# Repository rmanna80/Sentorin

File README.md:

# Sentorin

One platform for NFC/Bluetooth devices:

- **Pen** — tap to open the owner's business card; Bluetooth finding (BC832 / nRF52832).
- **Emergency bracelet** — tap opens an emergency page; full details only for verified responders, every view logged.

| Folder | Contents | Status |
|---|---|---|
| `hardware/pen-pcb` | KiCad project, revision 0.3 candidate | Not released for fabrication (see its README) |
| `backend/supabase` | Database schema, access rules, tests | Deployed to Supabase project `smartpen`; access tests pass there |
| `web/` | Tap pages (business card, emergency sign-in) | Written; not yet opened in a browser or hosted |
| `app/` | Owner app, iPhone + Android (Expo) | Typechecks and bundles; not yet run on a phone |
| `firmware/` | Pen firmware v1 beacon (nRF Connect SDK) | Written; not compiled or run on hardware |

## Backend tests

`backend/supabase/tests/local_auth_stub.sql` stands in for Supabase's auth schema on a plain Postgres.
Load the stub, then the migration, then run `access_rules_test.sql`.

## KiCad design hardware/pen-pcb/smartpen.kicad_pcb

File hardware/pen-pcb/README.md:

# Smart pen BLE tag — KiCad project, revision 0.3 candidate (NOT released for fabrication)

Open `smartpen.kicad_pro` in KiCad 7 or newer. No Gerbers, drill, CPL or STEP files are included:
ERC has not been run and the items under "Release blockers" are open.

## Changes in the 0.3 candidate (owner's measurement of Fanstel's EV-BC832 V2 Gerbers)

| Item | Fanstel EV board (owner-measured) | 0.2.1 | 0.3 candidate |
|---|---|---|---|
| Edge land, along the row | ~0.70 mm | 0.67 | **0.70** |
| Edge land, inner end (heel) from module centre | ~3.25 mm | 3.30 | **3.25** (matches) |
| Edge land, outer end (toe) from module centre | ~4.55 mm | 4.05 | **4.20** |
| Toe beyond the 7.8 mm module body | 0.65 mm | 0.15 | **0.30** |
| LGA land diameter | ~0.60 mm | 0.50 | **0.60** |
| Pitches (1.10 / 1.20 mm), pad counts | — | match | match |

- Fanstel's full land (toe at 4.55 mm) needs copper out to 9.1 mm plus edge clearance, i.e. a board about 9.6 mm wide, which does not fit even the 9.5 mm bore. The toe is therefore the one remaining deviation: 0.30 mm instead of 0.65 mm. Heel and width now follow Fanstel.
- **Board is now 8.9 mm wide and requires the 9.5 mm bore** (0.28 mm at the PCB corner; only 0.10 mm in a 9.14 mm bore).
- Strict antenna keep-out ends at x = 3.1 mm because Fanstel's first row of 0.6 mm LGA lands reaches x = 3.18 mm.
- DC/DC order confirmed by the owner from the EV-BC832 V2 schematic (DCC -> 10 uH -> 15 nH -> DEC4, SW7 on for V1). No change.
- Local result (KiCad 7.0.11): DRC 0 violations, 0 unconnected; netlist cross-check matches. **Re-run ERC and DRC in your KiCad.**
- The Gerber figures are the owner's; the designer has not seen the files. The module's own pad dimensions (not the EV board's lands) are still worth requesting from Fanstel to justify the 0.30 mm toe.

## Changes in 0.2.1 (from the owner's ERC/DRC run in a newer KiCad)

| Finding | Fix |
|---|---|
| DRC error: bottom GND pour reached the board edge (0.0005 mm, rule 0.25 mm). KiCad 7's scripted fill did not apply the edge rule and its DRC did not flag it | Pour outline is now drawn 0.3 mm inside the edge; the generator asserts the filled area stays clear |
| ERC: 0 errors, 16 warnings "symbol library 'smartpen' not configured" | Added `smartpen.kicad_sym` and `sym-lib-table` |
| DRC: 6 warnings "footprint does not match library copy" for stock parts | All footprints now come from the project library `smartpen.pretty` |
| L1/L2 order | Owner reports Fanstel's EV-BC832 V2 schematic shows 10 uH on the DCC side and 15 nH on the DEC4 side. This board is wired DCC -> L1 10 uH -> L2 15 nH -> DEC4, which agrees. Not read first-hand by the designer |
| L1 rating | Owner checked LBMF1608T100K: 80 mA rated, above Nordic's 50 mA minimum |

Local result after these fixes (KiCad 7.0.11): DRC 0 violations, 0 unconnected; netlist cross-check matches. **Re-run ERC and DRC in your KiCad to confirm.**

## Changes from revision 0.1

| Decision | What changed |
|---|---|
| Shorten the board | 12.35 mm -> **11.35 mm** (8.6 mm wide, unchanged) |
| Move Q1 | Q1 is now on the bottom; battery pads J1/J2 moved to the top rear strip |
| SWDIO via | Moved out of the 3.2 mm antenna strip |
| Fewer tracks under the module | The VDD lane that ran under pins 9-13 is gone; VDD drops to the bottom at pin 16. Top-side tracks under the module are now only the DCC/DEC4 escapes and the SWDCLK stub |
| Inductors | L1 = Taiyo Yuden LBMF1608T100K (10 uH 0603), L2 = Taiyo Yuden HK100515NJ-T (15 nH 0402) |
| MOSFET | AO3401A checked against the AOS datasheet (below) |
| Bore | Clearances now reported for both 9.14 mm and 9.50 mm |

## Validation status

| Check | Result | How |
|---|---|---|
| DRC | 0 violations locally after the 0.2.1 fixes; owner's run of 0.2 found 1 error (fixed) | KiCad 7.0.11 `WriteDRCReport`, `validation/drc_report.txt` |
| Schematic = board netlist | **Match** (8 nets, 13 parts) | `validation/netlist_crosscheck.txt` |
| ERC | Owner's run of 0.2: **0 errors**, 16 library warnings (addressed in 0.2.1) | re-run to confirm |
| AO3401A | Pin 1 gate, 2 source, 3 drain. RDS(on) < 85 mOhm at VGS = -2.5 V; threshold -0.5 to -1.3 V | AOS datasheet |
| DC/DC inductors | 10 uH is the buck inductor, 15 nH filters it; both required, in series between DCC and DEC4 | Nordic DevZone; **series order not confirmed against Fanstel's EV-BC832 schematic** |
| BC832 land pattern | **Not verified against Fanstel** (agrees across two independent community footprints) | compare with Fanstel Gerber/PADS files |
| Mechanical | Calculated only, `validation/mechanical_envelope.json` | — |
| RF, battery pulse, NFC | **Nothing measured** | — |

### MOSFET gate drive in this circuit (calculation)
Gate is tied to GND, so VGS = -VDD: about -3.1 V with fresh cells and -2.4 V at end of life.
-2.4 V is 0.1 V short of the datasheet's -2.5 V test point, so the 85 mOhm limit is not guaranteed there,
but it is 1.1 V beyond the worst-case threshold. At the 5.3 mA radio peak even 1 Ohm would drop only 5 mV.
With the cells reversed the gate sits above the source and the body diode is reverse-biased, so the load sees no reverse voltage.

## Mechanical (calculated, board centred on the bore axis)

| Feature | Clearance, 9.14 mm bore | Clearance, 9.50 mm bore |
|---|---|---|
| PCB corner (8.9 mm board) | 0.10 mm | 0.28 mm |
| BC832 top corner | 0.32 mm | 0.50 mm |
| Q1 body on the bottom (1.25 mm tall, outer edge 3.85 mm off-centre) | 0.38 mm | 0.56 mm |
| C1/C2 on the bottom | 1.46 mm | 1.64 mm |

JLCPCB's outline tolerance is +/-0.2 mm. **The 9.50 mm bore is now required.**

### Proposed battery/contact stack-up (nominal, to be designed in CAD and measured)

| Element | Length |
|---|---|
| PCB | 11.35 mm |
| BAT+ contact: formed spring tab soldered to J1, reaching the bore axis | 1.0 mm |
| Cell 1 (can = positive, facing the board) | 2.66 mm max |
| Cell 2 | 2.66 mm max |
| BAT- conical spring in the rear cap, working height | 1.2 mm |
| Left for cap face and tolerances | **1.43 mm** of 20.3 mm |

- The cell cans are positive on their side walls, so the cells need an insulating sleeve (about 7.0 mm ID) inside the metal barrel.
- Negative return from the cap spring to J2: either the metal rear barrel plus a wiper contact on J2, or a strip along the sleeve. Not decided.
- The module (8.8 mm) sits fully inside the 10 mm plastic front section; the last 1.35 mm of the board is inside the metal barrel.
- The cap must be child-resistant (tool or two simultaneous motions). Check current button-cell regulations for your markets.

## Release blockers

1. **ERC** in KiCad.
2. **BC832 footprint** against Fanstel's files; **L1/L2 series order** against the EV-BC832 schematic.
3. **Battery pulse test** (treat as blocking). Suggested bench test before any pen is built: power the board from a supply through a series resistor to emulate the cells: 3.1 V / 30 Ohm (fresh) and 2.4 V / 180 Ohm (end of life, datasheet worst-case resistance). Scope VDD during advertising at 0 dBm. Pass: VDD stays above 1.9 V and no resets over 10,000 events. Repeat with real cells at room temperature and at 0 C.
4. **Bulk capacitor leakage and real capacitance at 3 V** on the chosen 47 uF part.
5. **Antenna**: pins 1 (GND), 3 (SWDIO) and 16 (VDD) sit beside the antenna, so their lands, three short tracks and the GND via remain inside the strip. Range-test in a representative housing.
6. **Castellated lands** have a 0.30 mm toe (Fanstel EV board: 0.65 mm): reflow only; confirm joint quality on first articles.
7. **Contact stack-up, sleeve, cap** designed and measured.
8. **NFC tag** in the plastic cap selected and read-tested with several phones.
9. Remaining BOM lines marked "from memory" confirmed.

## Regenerating

`generator/build_pcb.py` then `generator/build_sch.py` (KiCad 7 Python). Both read one netlist.

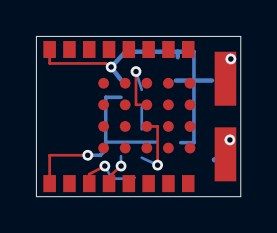
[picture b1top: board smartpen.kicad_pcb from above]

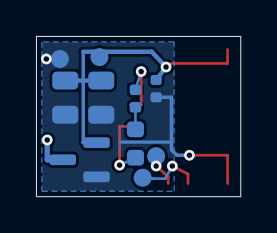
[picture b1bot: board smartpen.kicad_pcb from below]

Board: 2 copper layers, 11.3 x 8.9 mm, 13 parts (10 on the bottom side), 8 nets.

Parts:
C1, C2: 47u; C_0805_2012Metric
C3: 100n; C_0402_1005Metric
J1: BAT+; BatteryPad_1.2x3.0mm
J2: BAT-; BatteryPad_1.2x3.0mm
L1: 10u; L_0603_1608Metric
L2: 15n; L_0402_1005Metric
Q1: AO3401A; SOT-23
TP1: SWDIO; TestPad_D1.0mm
TP2: SWDCLK; TestPad_D1.0mm
TP4: VDD; TestPad_D1.0mm
TP5: GND; TestPad_D1.0mm
U1: BC832 (V1); BC832_V1_pen

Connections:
DCC: L1.1, U1.B3
DCDC_MID: L1.2, L2.1
DEC4: L2.2, U1.C3
GND: C1.2, C2.2, C3.2, J2.1, Q1.1, TP5.1, U1.1
SWDCLK: TP2.1, U1.4
SWDIO: TP1.1, U1.3
VBAT: J1.1, Q1.3
VDD: C1.1, C2.1, C3.1, Q1.2, TP4.1, U1.16

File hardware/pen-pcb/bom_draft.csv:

Ref,Qty,Value,Package,Manufacturer part number,Side,Verification status
U1,1,BC832 V1 BLE module,7.8x8.8 mm castellated+LGA,Fanstel BC832 (V1 revision),Top,Pinout per Fanstel datasheet; land pattern NOT checked against Fanstel files
Q1,1,P-MOSFET 30 V,SOT-23,AOS AO3401A (LCSC C15127),Bottom,Verified against AOS datasheet: G1/S2/D3; RDS(on) < 85 mOhm at VGS -2.5 V
L1,1,10 uH,0603,Taiyo Yuden LBMF1608T100K,Bottom,80 mA rated per owner's datasheet check (Nordic minimum 50 mA)
L2,1,15 nH,0402,Taiyo Yuden HK100515NJ-T,Bottom,Named in the same Nordic DevZone thread; confirm on datasheet
C1 C2,2,47 uF 6.3 V X5R,0805,Murata GRM21BR60J476ME15L,Bottom,From memory - confirm; measure leakage and capacitance at 3 V bias
C3,1,100 nF 16 V X7R,0402,Samsung CL05B104KO5NNNC,Bottom,From memory - confirm
J1 J2,2,Battery contact pads 1.2x3.0 mm,PCB pad,n/a (custom formed contacts),Top rear,Contact parts not designed
TP1 TP2 TP4 TP5,4,Test pads 1.0 mm,PCB pad,n/a,Bottom,-
